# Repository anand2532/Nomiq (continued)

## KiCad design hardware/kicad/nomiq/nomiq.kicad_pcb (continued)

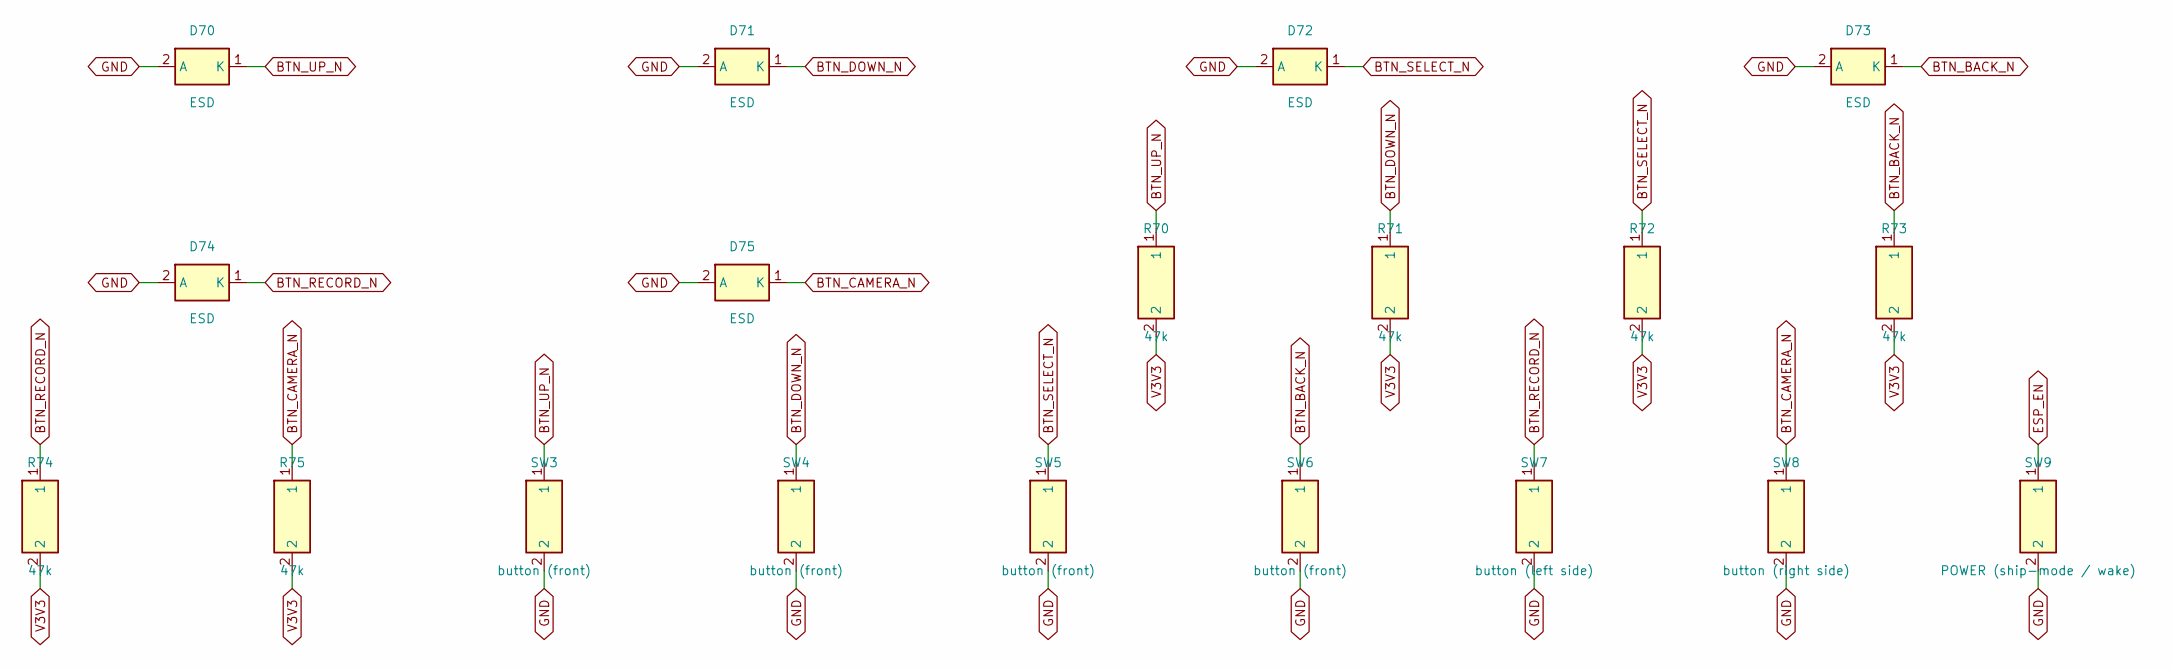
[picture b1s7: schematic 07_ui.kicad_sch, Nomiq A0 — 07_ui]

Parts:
D70, D71, D72, D73, D74, D75: ESD; D_SOD-882; MPN Nexperia PESD5V0S1BL
R70, R71, R72, R73, R74, R75: 47k; R_0402_1005Metric
SW3, SW4, SW5, SW6: button (front); SW_SPST_PTS810; MPN C&K PTS810 SJM 250 SMTR LFS
SW7: button (left side); SW_SPST_EVQP7A; MPN Panasonic EVQ-P7A01P
SW8: button (right side); SW_SPST_EVQP7A; MPN Panasonic EVQ-P7A01P
SW9: POWER (ship-mode / wake); SW_SPST_EVQP7A; MPN Panasonic EVQ-P7A01P

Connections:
BTN_BACK_N: D73.1 (K), R73.1, SW6.1; also elsewhere on the board
BTN_CAMERA_N: D75.1 (K), R75.1, SW8.1; also elsewhere on the board
BTN_DOWN_N: D71.1 (K), R71.1, SW4.1; also elsewhere on the board
BTN_RECORD_N: D74.1 (K), R74.1, SW7.1; also elsewhere on the board
BTN_SELECT_N: D72.1 (K), R72.1, SW5.1; also elsewhere on the board
BTN_UP_N: D70.1 (K), R70.1, SW3.1; also elsewhere on the board
ESP_EN: SW9.1; also elsewhere on the board
GND: D70.2 (A), D71.2 (A), D72.2 (A), D73.2 (A), D74.2 (A), D75.2 (A), SW3.2, SW4.2, SW5.2, SW6.2, SW7.2, SW8.2, SW9.2; also elsewhere on the board
V3V3: R70.2, R71.2, R72.2, R73.2, R74.2, R75.2; also elsewhere on the board

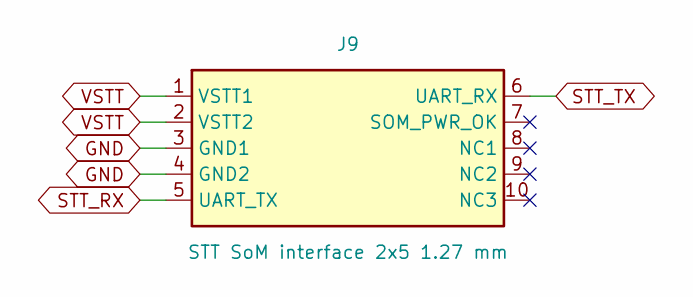
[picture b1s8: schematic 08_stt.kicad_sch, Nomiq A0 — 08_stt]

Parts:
J9: STT SoM interface 2x5 1.27 mm; PinHeader_2x05_P1.27mm_Vertical_SMD; MPN Samtec FTSH-105-01-L-DV

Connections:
GND: J9.3 (GND1), J9.4 (GND2); also elsewhere on the board
STT_RX: J9.5 (UART_TX); also elsewhere on the board
STT_TX: J9.6 (UART_RX); also elsewhere on the board
VSTT: J9.1 (VSTT1), J9.2 (VSTT2); also elsewhere on the board

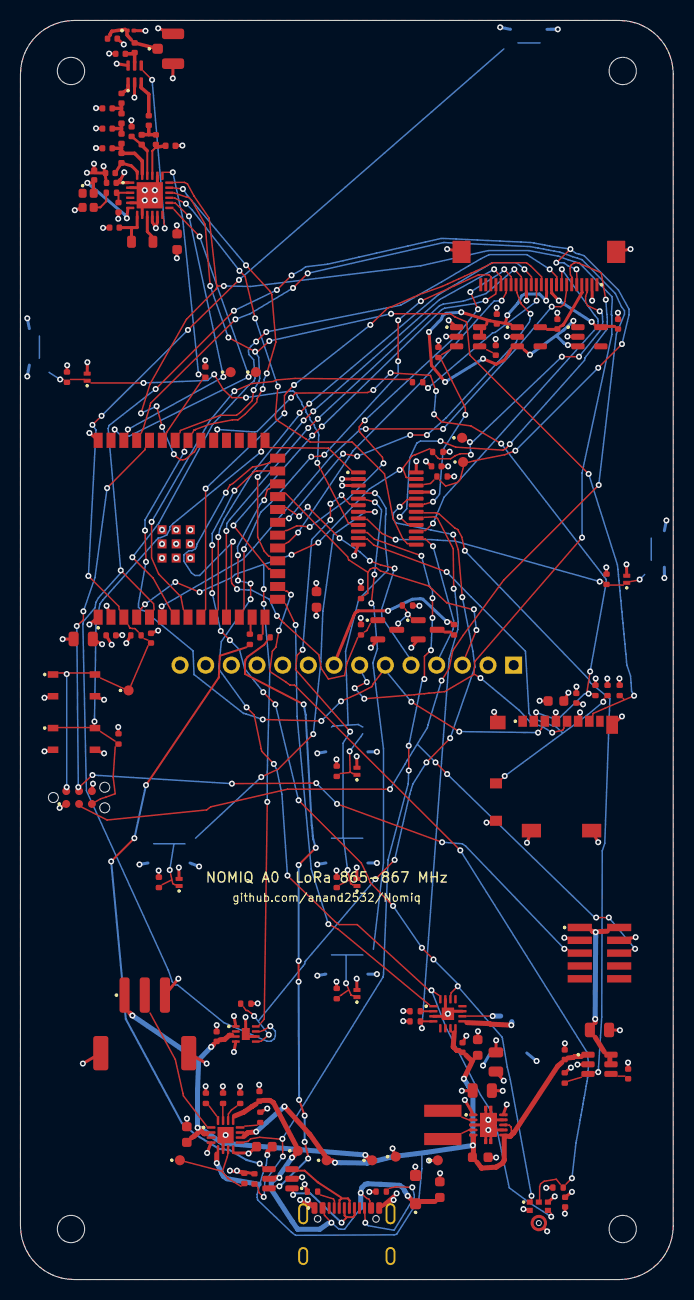
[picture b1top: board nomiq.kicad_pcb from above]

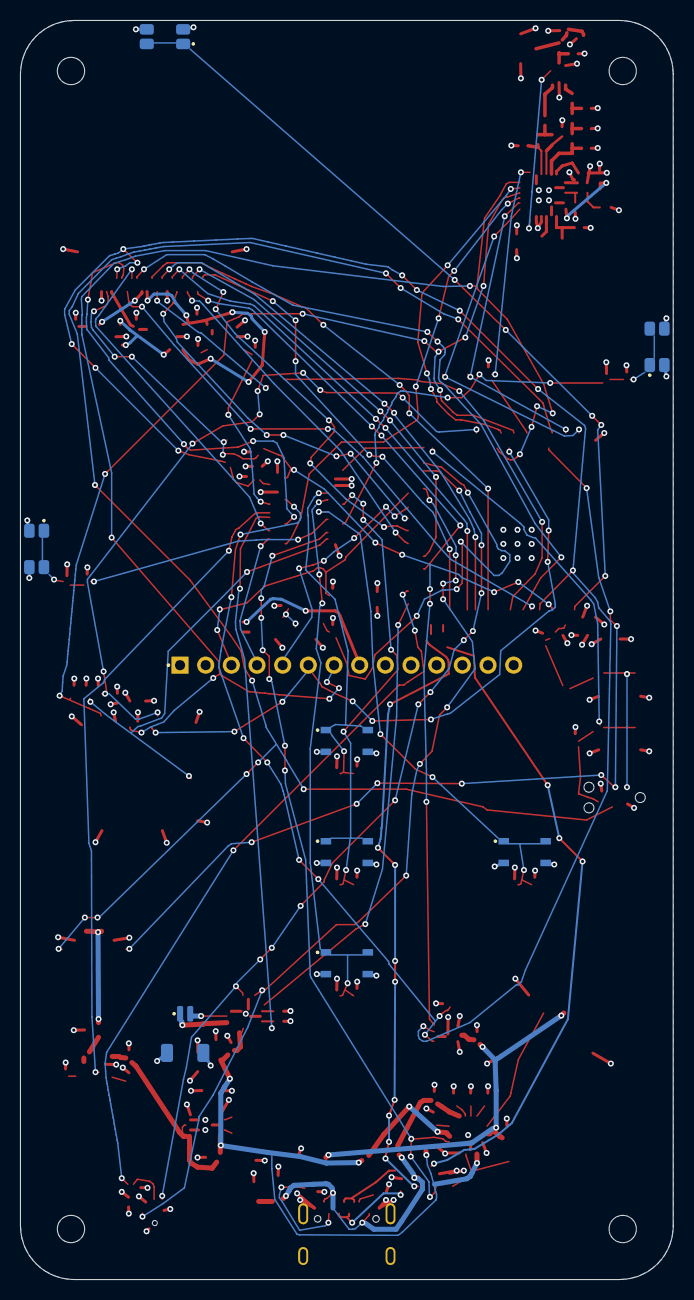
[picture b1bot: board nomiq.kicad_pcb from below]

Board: 4 copper layers, 64.6 x 124.6 mm, 142 parts (9 on the bottom side), 99 nets.

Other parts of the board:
H1, H2, H3, H4: MountingHole; MountingHole_2.7mm_M2.5

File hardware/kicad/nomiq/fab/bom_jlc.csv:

Comment,Designator,Footprint,LCSC Part #
USB-C 16P (GCT USB4105-GF-A),J1,USB_C_Receptacle_GCT_USB4105-xx-A_16P_TopMnt_Horizontal,
5.1k,"R1,R2",R_0402_1005Metric,
USBLC6-2SC6 (STMicro USBLC6-2SC6),D1,SOT-23-6,C7519
SMF5.0A (Littelfuse SMF5.0A),D2,D_SOD-123F,
10uF/10V,"C1,C6,C41",C_0603_1608Metric,
BQ24074 (TI BQ24074RGTR),U8,VQFN-16-1EP_3x3mm_P0.5mm_EP1.6x1.6mm,C54313
887R 1%,R3,R_0402_1005Metric,
1.13k 1%,R4,R_0402_1005Metric,
2.94k 1%,R5,R_0402_1005Metric,
37.4k 1%,R6,R_0402_1005Metric,
100k,"R7,R8,R9,R13,R40,R41,R43,R50,R61",R_0402_1005Metric,
1uF/10V,"C2,C5,C10",C_0402_1005Metric,
4.7uF/10V,"C3,C4",C_0603_1608Metric,
"Battery JST-PH 3P (+, NTC, -) (JST S3B-PH-SM4-TB)",J2,JST_PH_S3B-PH-SM4-TB_1x03-1MP_P2.00mm_Horizontal,
MAX17048 (Analog Devices MAX17048G+T10),U9,TDFN-8-1EP_2x2mm_P0.5mm_EP0.8x1.2mm,C2682616
TPS63001 (TI TPS63001DRCR),U10,Texas_S-PVSON-N10,C28060
2.2uH (Taiyo Yuden NRS4018T2R2MDGJ),L1,L_Taiyo-Yuden_NR-40xx,
22uF/6.3V,"C7,C8,C21",C_0805_2012Metric,
TPS22918 (STT rail) (TI TPS22918DBVR),U14,SOT-23-6,
1nF,"C9,C50",C_0402_1005Metric,
22uF/10V,C11,C_0805_2012Metric,
ESP32-S3-WROOM-1-N16R8 (Espressif ESP32-S3-WROOM-1-N16R8),U1,ESP32-S3-WROOM-1,C2913202
10k,"R20,R21,R30,R66,R62,R63",R_0402_1005Metric,
1uF,"C20,C51,C52,C53",C_0402_1005Metric,
0.1uF,"C22,C23,C32,C35,C40,C42,C62",C_0402_1005Metric,
RESET (C&K PTS810 SJM 250 SMTR LFS),SW1,SW_SPST_PTS810,
BOOT (C&K PTS810 SJM 250 SMTR LFS),SW2,SW_SPST_PTS810,
0R,"R22,R23",R_0402_1005Metric,
TCA9535 (TI TCA9535PWR),U4,TSSOP-24_4.4x7.8mm_P0.65mm,C130204
2.2k,"R24,R25",R_0402_1005Metric,
SX1262 (Semtech SX1262IMLTRT),U2,QFN-24-1EP_4x4mm_P0.5mm_EP2.6x2.6mm,C191341
15uH (Murata LQM21FN150M70L),L2,L_0805_2012Metric,
470nF,C30,C_0402_1005Metric,
47nF,C31,C_0402_1005Metric,
10uF/6.3V,"C33,C60,C61",C_0603_1608Metric,
TCXO 32 MHz 1.8 V ±2 ppm (Epson TG2016SMN 32.0000M-ECGNNM3),Y1,Crystal_SMD_2016-4Pin_2.0x1.6mm,
220R,R31,R_0402_1005Metric,
10pF,C34,C_0402_1005Metric,
PE4259 (pSemi PE4259-63),U3,SOT-363_SC-70-6,C470892
47nH (Murata LQW15AN47NJ00),L3,L_0402_1005Metric,
4.7pF,C36,C_0402_1005Metric,
12nH (Murata LQW15AN12NJ00),"L4,L5",L_0402_1005Metric,
6.8pF,C37,C_0402_1005Metric,
3.3pF,C38,C_0402_1005Metric,
47pF,"C39,C43",C_0402_1005Metric,
2.7pF,"C44,C45",C_0402_1005Metric,
27nH (Murata LQW15AN27NJ00),"L6,L7",L_0402_1005Metric,
100pF,C47,C_0402_1005Metric,
u.FL (Hirose U.FL-R-SMT-1(10)),J4,U.FL_Hirose_U.FL-R-SMT-1_Vertical,
ESD RF (low C) (Infineon ESD0P2RF-02LS),D3,D_0201_0603Metric,
ICS-43434 (TDK InvenSense ICS-43434),U5,InvenSense_ICS-43434-6_3.5x2.65mm,C5656610
MAX98357A (Analog Devices MAX98357AETE+T),U6,TQFN-16-1EP_3x3mm_P0.5mm_EP1.23x1.23mm,C910544
Speaker JST-SH 2P (JST SM02B-SRSS-TB),J5,JST_SH_SM02B-SRSS-TB_1x02-1MP_P1.00mm_Horizontal,
OV2640 24P FPC 0.5 mm (Hirose FH12-24S-0.5SH(55)),J6,Hirose_FH12-24S-0.5SH_1x24-1MP_P0.50mm_Horizontal,
TLV75528 (2.8 V) (TI TLV75528PDBVR),U12,SOT-23-5,
TLV75512 (1.2 V) (TI TLV75512PDBVR),U13,SOT-23-5,
TPS22918 (cam 3V3) (TI TPS22918DBVR),U15,SOT-23-6,
33R,R51,R_0402_1005Metric,
"TFT 2.4in ILI9341 SPI module (14-pin) (2.4in 240x320 ILI9341 SPI module, 1x14 2.54 mm)",J7,TFT_2.4in_ILI9341_1x14,
"2N7002 (Nexperia 2N7002,215)",Q2,SOT-23,C8545
AO3401A (AOS AO3401A),Q1,SOT-23,C15127
4.7R,R60,R_0402_1005Metric,
microSD push-push (Molex 104031-0811),J8,microSD_HC_Molex_104031-0811,
47k,"R64,R65,R70,R71,R72,R73,R74,R75",R_0402_1005Metric,
button (front) (C&K PTS810 SJM 250 SMTR LFS),"SW3,SW4,SW5,SW6",SW_SPST_PTS810,
ESD (Nexperia PESD5V0S1BL),"D70,D71,D72,D73,D74,D75",D_SOD-882,
button (left side) (Panasonic EVQ-P7A01P),SW7,SW_SPST_EVQP7A,
button (right side) (Panasonic EVQ-P7A01P),SW8,SW_SPST_EVQP7A,
POWER (ship-mode / wake) (Panasonic EVQ-P7A01P),SW9,SW_SPST_EVQP7A,
STT SoM interface 2x5 1.27 mm (Samtec FTSH-105-01-L-DV),J9,PinHeader_2x05_P1.27mm_Vertical_SMD,

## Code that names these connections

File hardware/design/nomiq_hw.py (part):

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conn("ESP_EN", "SW1.1"); conn("GND", "SW1.2")
part("SW2", "BOOT", "C&K PTS810 SJM 250 SMTR LFS", S, pins=["1", "2"], footprint="Button_Switch_SMD:SW_SPST_PTS810")
conn("IOX_INT_N", "SW2.1"); conn("GND", "SW2.2")
R("R21", "10k", S, "IOX_INT_N", "V3V3", note="GPIO0 strap: high = SPI boot")
# USB
R("R22", "0R", S, "USB_DP_MCU", "ESP_USB_DP", note="series, placeholder for EMI filter")
R("R23", "0R", S, "USB_DN_MCU", "ESP_USB_DN")
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Cap("C34", "10pF", S, "SX_XTA", verify=True, note="XTA load per Semtech TCXO guidance (tune)")
conn("TCXO_OUT", "Y1.OUT"); conn("SX_XTA", "U2.XTA")
Cap("C35", "0.1uF", S, "TCXO_VCC")
part("U3", "PE4259", "pSemi PE4259-63", S, pins=["RF1", "RF2", "RFC", "CTRL", "VDD", "GND"], power=["VDD", "GND"],
     footprint="Package_TO_SOT_SMD:SOT-363_SC-70-6", note="SPDT, single-pin mode (pin 6 = VDD): CTRL high -> RFC-RF1 (TX)",
     pads={"RF1": "1", "GND": "2", "RF2": "3", "CTRL": "4", "RFC": "5", "VDD": "6"})
conn("V3V3", "U3.VDD"); conn("GND", "U3.GND"); conn("RF_SW_CTRL", "U3.CTRL")
conn("RF_TX", "U3.RF1"); conn("RF_RX", "U3.RF2"); conn("RF_ANT", "U3.RFC")
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Cap("C37", "6.8pF", S, "TX_N1", verify=True, note="low-pass shunt 1")
L("L5", "12nH", "Murata LQW15AN12NJ00", S, "TX_N1", "TX_N2", verify=True, note="low-pass series 2")
Cap("C38", "3.3pF", S, "TX_N2", verify=True, note="low-pass shunt 2")
Cap("C39", "47pF", S, "TX_N2", "RF_TX", note="DC block (PE4259 RF1 must be DC-free)")
conn("SX_RFO", "U2.RFO")
# --- RX: lattice balun RF_RX -> RFI_P / RFI_N ---
Cap("C43", "47pF", S, "RF_RX", "RX_IN", note="DC block (PE4259 RF2)")
Cap("C44", "2.7pF", S, "RX_IN", "SX_RFI_P", verify=True, note="balun series C")
L("L6", "27nH", "Murata LQW15AN27NJ00", S, "RX_IN", "SX_RFI_N", verify=True, note="balun series L")
L("L7", "27nH", "Murata LQW15AN27NJ00", S, "SX_RFI_P", "GND", verify=True, note="balun shunt L")
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conn("SX_RFI_P", "U2.RFI_P"); conn("SX_RFI_N", "U2.RFI_N")
# --- antenna port: DC block + pi tuning pads ---
Cap("C46", "DNP", S, "RF_ANT", note="antenna pi-match shunt 1 (tuning, not fitted)", dnp=True)
Cap("C47", "100pF", S, "RF_ANT", "RF_ANT_CONN", note="series DC block (PE4259 RFC)")
Cap("C48", "DNP", S, "RF_ANT_CONN", note="antenna pi-match shunt 2 (tuning, not fitted)", dnp=True)
part("J4", "u.FL", "Hirose U.FL-R-SMT-1(10)", S, pins=["SIG", "GND"], footprint="Connector_Coaxial:U.FL_Hirose_U.FL-R-SMT-1_Vertical",
     pads={"SIG": "1", "GND": "2"}, note="pigtail to bulkhead SMA in the top end cap")
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conn("V3V3", "U5.VDD"); conn("GND", "U5.GND", "U5.LR")
conn("I2S_BCLK", "U5.SCK"); conn("I2S_WS", "U5.WS"); conn("I2S_DIN", "U5.SD")
Cap("C40", "0.1uF", S, "V3V3")
R("R40", "100k", S, "I2S_DIN", "GND", note="keeps GPIO46 strap low when mic is tri-stated")
part("U6", "MAX98357A", "Analog Devices MAX98357AETE+T", S,
     pins=["VDD", "GND", "BCLK", "LRCLK", "DIN", "GAIN_SLOT", "SD_MODE", "OUTP", "OUTN", "EP", "NC1", "NC2", "NC3", "NC4"],
     power=["VDD", "GND", "EP"], nc=["NC1", "NC2", "NC3", "NC4"], footprint="Package_DFN_QFN:TQFN-16-1EP_3x3mm_P0.5mm_EP1.23x1.23mm",
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conn("V3V3", "J7.VCC"); conn("GND", "J7.GND")
conn("LCD_CS", "J7.CS"); conn("LCD_RST_N", "J7.RESET"); conn("LCD_DC", "J7.DC"); conn("SPI_MOSI", "J7.SDI")
conn("SPI_SCK", "J7.SCK")
# backlight: LCD_BL (GPIO45, strap low) -> Q2 N-FET -> Q1 P-FET high side -> R60 -> module LED pin
part("Q2", "2N7002", "Nexperia 2N7002,215", S, pins=["G", "S", "D"], footprint="Package_TO_SOT_SMD:SOT-23",
     pads={"G": "1", "S": "2", "D": "3"})
conn("LCD_BL", "Q2.G"); conn("GND", "Q2.S"); conn("LCD_BL_G", "Q2.D")
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R("R66", "10k", S, "LCD_BL_G", "V3V3", note="P-FET gate pull-up: backlight off unless Q2 on")
R("R60", "4.7R", S, "LCD_LED_SW", "LCD_LED", note="extra series resistance; module has its own LED resistor/transistor", verify=True)
conn("LCD_LED", "J7.LED")
R("R61", "100k", S, "LCD_BL", "GND", note="GPIO45 strap must be LOW at reset")
R("R62", "10k", S, "LCD_CS", "V3V3")
Cap("C60", "10uF/6.3V", S, "V3V3", fp="Capacitor_SMD:C_0603_1608Metric")
part("J8", "microSD push-push", "Molex 104031-0811", S,
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
# map board_pins.h macro -> expected net
PIN_MACRO_NET = {
    "PIN_SPI_SCK": "SPI_SCK", "PIN_SPI_MOSI": "SPI_MOSI", "PIN_SPI_MISO": "SPI_MISO", "PIN_LORA_NSS": "LORA_NSS",
    "PIN_LORA_BUSY": "LORA_BUSY", "PIN_LORA_DIO1": "LORA_DIO1", "PIN_LCD_CS": "LCD_CS", "PIN_LCD_DC": "LCD_DC",
    "PIN_LCD_BL": "LCD_BL", "PIN_SD_CS": "SD_CS", "PIN_I2C_SDA": "I2C_SDA", "PIN_I2C_SCL": "I2C_SCL",
    "PIN_IOX_INT": "IOX_INT_N", "PIN_I2S_BCLK": "I2S_BCLK", "PIN_I2S_WS": "I2S_WS", "PIN_I2S_DIN": "I2S_DIN",
    "PIN_I2S_DOUT": "I2S_DOUT", "PIN_CAM_XCLK": "CAM_XCLK_MCU", "PIN_CAM_VSYNC": "CAM_VSYNC",
    "PIN_CAM_HREF": "CAM_HREF", "PIN_CAM_PCLK": "CAM_PCLK", "PIN_STT_TX": "STT_TX", "PIN_STT_RX": "STT_RX",
    **{f"PIN_CAM_D{i}": f"CAM_D{i}" for i in range(8)},
}
IOX_MACRO_NET = {
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        return any(PARTS[m.split('.')[0]].value.split()[0].endswith(("k", "R")) and
                   any(n == other for n, mm in NETS.items() if f"{m.split('.')[0]}.2" in mm or f"{m.split('.')[0]}.1" in mm)
                   for m in NETS[net] if m.split('.')[0].startswith("R"))
    if not has_res("IOX_INT_N", "V3V3"): errs.append("GPIO0 strap needs a pull-up")
    if not has_res("LCD_BL", "GND"): errs.append("GPIO45 strap needs a pull-down (VDD_SPI 3.3 V)")
    if not has_res("I2S_DIN", "GND"): errs.append("GPIO46 strap needs a pull-down")
    return errs


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
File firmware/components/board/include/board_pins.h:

/* Board pin map — MUST match docs/02-hardware-architecture.md §2 (draft v0.1). */
#pragma once

/* Shared SPI2 bus: SX1262, TFT, microSD */
#define PIN_SPI_SCK      39
#define PIN_SPI_MOSI     40
#define PIN_SPI_MISO     41

/* SX1262 */
#define PIN_LORA_NSS     42
#define PIN_LORA_BUSY     2
#define PIN_LORA_DIO1     1
/* LORA_NRST on IO-expander P10 */

/* TFT */
#define PIN_LCD_CS       21
#define PIN_LCD_DC       14
#define PIN_LCD_BL       45   /* strap pin: keep low at reset */

/* microSD (SPI mode) */
#define PIN_SD_CS        38

/* I2C0 — expander, fuel gauge, OV2640 SCCB */
#define PIN_I2C_SDA       4
#define PIN_I2C_SCL       5
#define PIN_IOX_INT       0   /* strap pin: open-drain, idle high */

/* I2S0 full duplex */
#define PIN_I2S_BCLK     47
#define PIN_I2S_WS       48
#define PIN_I2S_DIN      46   /* from mic */
#define PIN_I2S_DOUT      3   /* to amp  */

/* OV2640 DVP (ESP32-S3-EYE compatible) */
#define PIN_CAM_XCLK     15
#define PIN_CAM_VSYNC     6
#define PIN_CAM_HREF      7
#define PIN_CAM_PCLK     13
#define PIN_CAM_D0       11
#define PIN_CAM_D1        9
#define PIN_CAM_D2        8
#define PIN_CAM_D3       10
#define PIN_CAM_D4       12
#define PIN_CAM_D5       18
#define PIN_CAM_D6       17
#define PIN_CAM_D7       16

/* UART0 to STT co-processor */
#define PIN_STT_TX       43
#define PIN_STT_RX       44

/* TCA9535 expander bits (port0 = P00..P07, port1 = P10..P17 -> bit 8..15) */
#define IOX_ADDR          0x20
#define IOX_BTN_UP        0
#define IOX_BTN_DOWN      1
#define IOX_BTN_SELECT    2
#define IOX_BTN_BACK      3
#define IOX_BTN_RECORD    4
#define IOX_BTN_CAMERA    5
#define IOX_CHG_STAT      6
#define IOX_SD_DETECT     7
#define IOX_LORA_NRST     8
#define IOX_LCD_RST       9
#define IOX_CAM_PWDN     10
#define IOX_CAM_RESET    11
#define IOX_AMP_SD       12
#define IOX_STT_EN       13
#define IOX_CAM_PWR_EN   14

/* Radio defaults — see docs/specs/lora-link-budget.md */
#define LORA_FREQ_HZ_DEFAULT   865062500UL
#define LORA_BW_KHZ            125     /* India: carrier BW <= 200 kHz */
#define LORA_SF_CONTROL        9
#define LORA_TX_DBM_MAX        22

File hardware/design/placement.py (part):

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    # TCXO + DC-DC: hand-placed and hand-routed (HAND_TRACKS in gen_pcb.py)
    place("Y1", -25.6, -44.5, 270)                         # OUT (pad 3) faces R31, VCC (pad 4) above it
    place("C35", -25.0, -47.0, 90)
    place("R31", -23.3, -45.25, 0)                         # TCXO_OUT -> XTA (pin 3)
    place("C34", -22.6, -43.8, 270)
    place("L2", -20.25, -40.4, 180)                        # pad1 DCC_SW under pin 9, pad2 VREG under pin 7
    place("C30", -23.0, -41.8, 180)
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    place("U6", 10.0, 36.0, 0)
    near("C42", "U6", "VDD", 1.2, 1.9, 90)
    near("C41", "U6", "VDD", 2.6, 1.9, 90)
    place("R41", 6.76, 35.75, 180)                         # pad1 AMP_GAIN next to pin 2
    place("R43", 6.76, 36.75, 180)                         # pad1 AMP_SD_N next to pin 4
    place("U5", 19.0, 56.0, 0)                             # mic: port hole -> front-face mic hole (MIC_X/MIC_Y)
    near("C40", "U5", "VDD", 1.7, 0.0, 90)
    place("R40", 20.9, 53.2, 90)                           # I2S_DIN pull-down, right of the mic (keeps WS exit free)
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    near("C5", "U9", "VDD", -1.9, 0.0, 90)
    place("R9", -10.0, 35.0, 0)
    place("U10", 14.0, 47.0, 0)                            # buck-boost: L1/L2/VIN/VOUT pins on the left
    place("L1", 9.5, 47.0, 90)                             # pad1 BB_L1 (pin 4, lower), pad2 BB_L2 (pin 2, upper)
    place("C6", 13.2, 50.2, 0)                             # VIN, next to pin 5
    place("C7", 13.4, 43.6, 0)                             # VOUT, next to pin 1
    place("C8", 13.4, 41.8, 0)
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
